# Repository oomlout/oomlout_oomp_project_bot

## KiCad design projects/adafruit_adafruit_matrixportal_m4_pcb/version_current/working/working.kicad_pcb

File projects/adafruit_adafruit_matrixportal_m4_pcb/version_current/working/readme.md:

# Adafruit-MatrixPortal-M4-PCB by adafruit  
This is a harvested standardized copy of a project from github.  
The original project can be found at:  
https://github.com/adafruit/Adafruit-MatrixPortal-M4-PCB  
Please consult that link for additional, details, files, and license information.  
Note: It was auto harvested and if the original repo had more than one board file or anything out of the ordinary the files here are likely not representative.

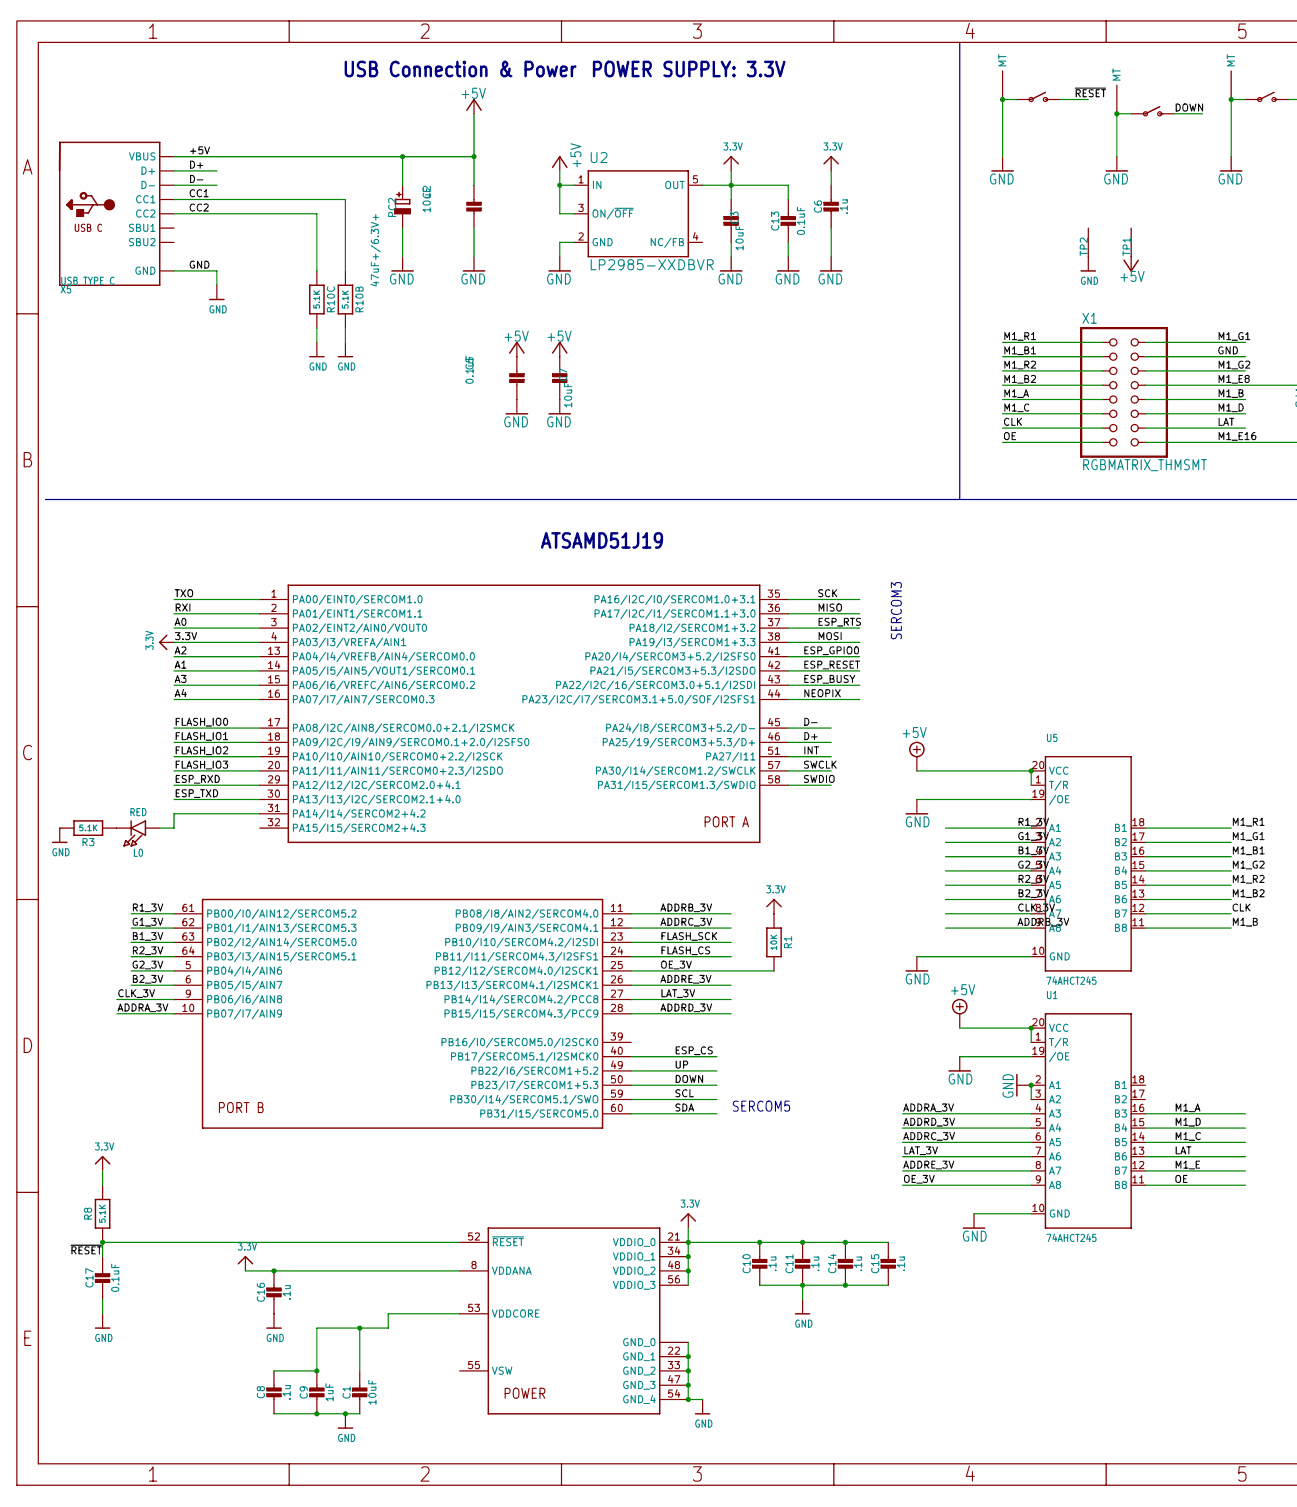
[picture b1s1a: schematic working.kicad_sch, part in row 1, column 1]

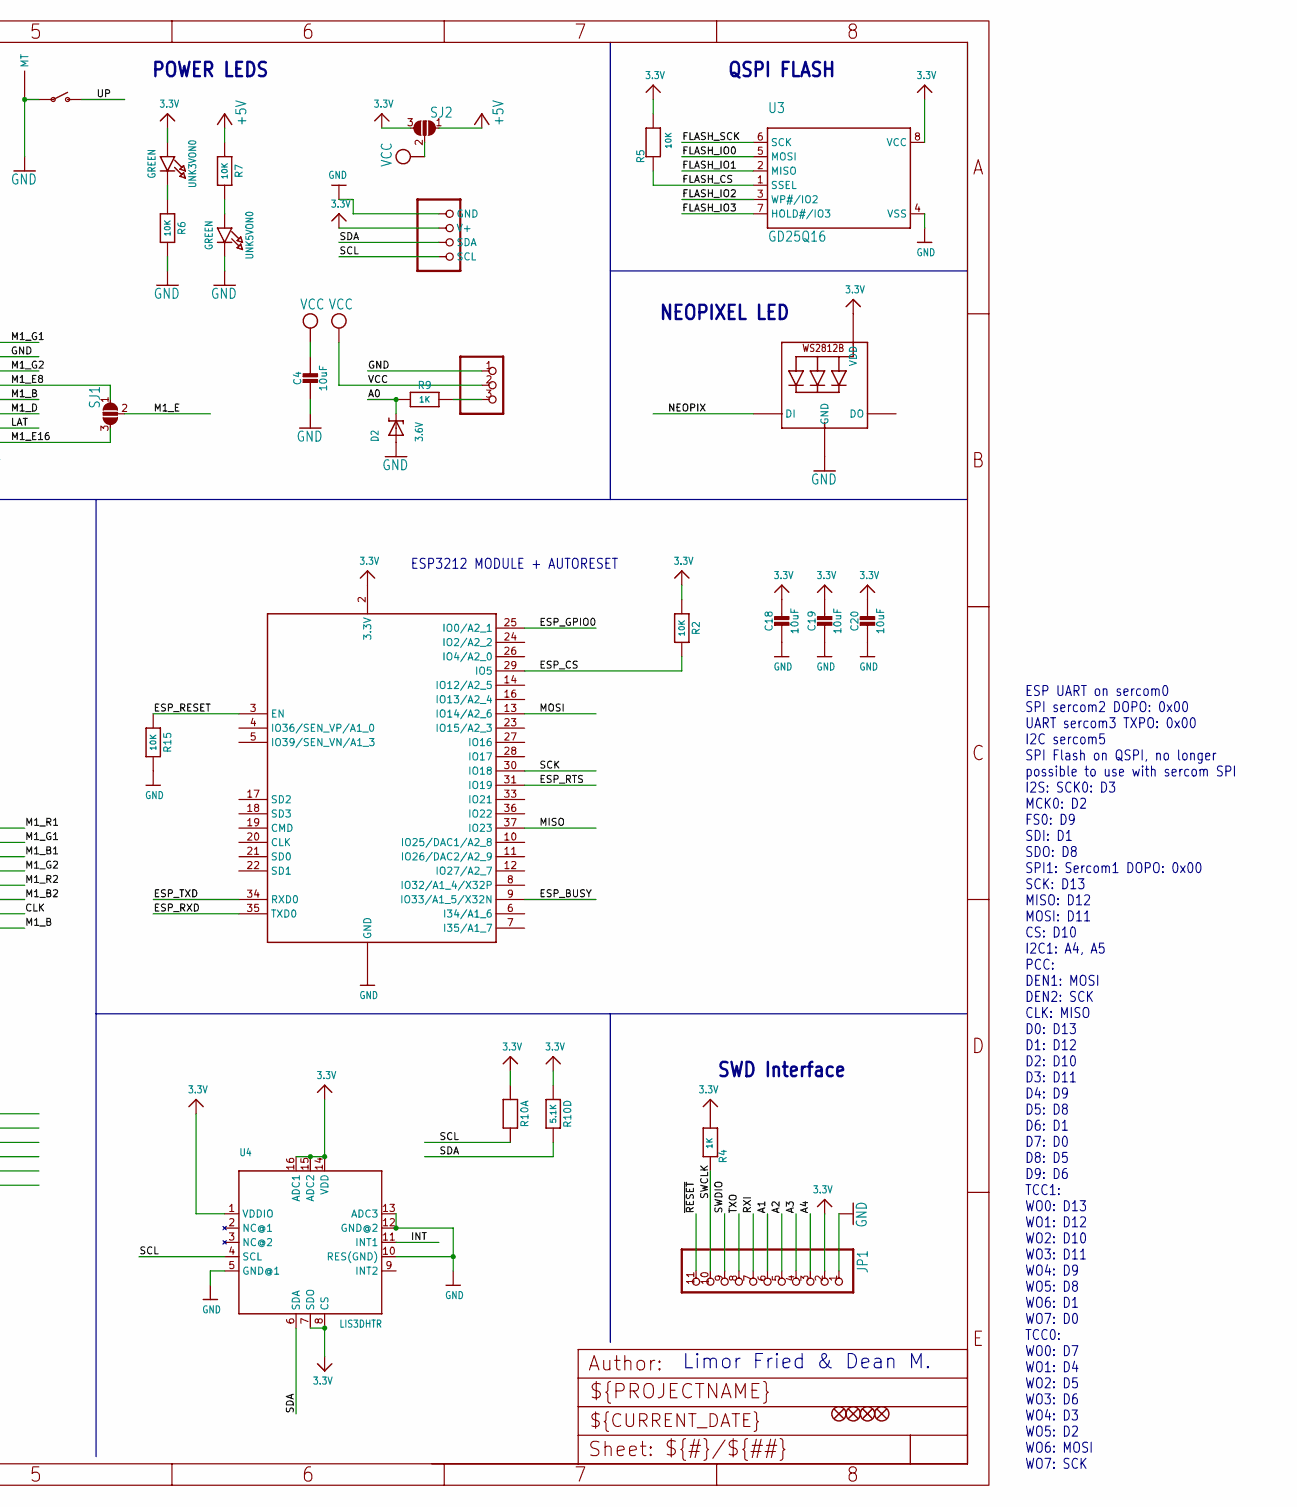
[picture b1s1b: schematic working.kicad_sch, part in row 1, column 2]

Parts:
C1, C2, C3, C4, C7, C18, C19, C20: 10uF; 0805-NO
C5, C13, C17: 0.1uF; 0603-NO
C6, C8, C10, C11, C14, C15, C16: .1u; 0603-NO
C9: 1uF; 0603-NO
CONN1: STEMMA_I2C_QT; JST_SH4
D2: 3.6V; SOD-323
DOWN0: TL3330AF260QG; SPST_TACTILE_RA
FID1, FID2, FID3, FID4: FIDUCIAL_1MM
JP1: HEADER-1X11; 1X11_ROUND
L0: RED; CHIPLED_0603_NOOUTLINE
LED1: WS2812B3535; LED3535
PC2: 47uF+/6.3V+; PANASONIC_D
R1, R2, R5, R6, R7, R15: 10K; 0603-NO
R3, R8: 5.1K; 0603-NO
R4, R9: 1K; 0603-NO
R10: 5.1K; RESPACK_4X0603
RST0: TL3330AF260QG; SPST_TACTILE_RA
SENSE0: JST PH 3; JSTPH3
SJ1, SJ2: SOLDERJUMPER_2WAY; SOLDERJUMPER_2WAY_OPEN_NOPASTE
TP1, TP2: SEWTAP_SMTNUTM3; SMT_NUT_3MM
U1, U5: 74AHCT245; TSSOP20
U2: LP2985-XXDBVR; SOT23-DBV
U3: GD25Q16; SOIC8_208MIL
U4: LIS3DHTR; LGA16_3X3MM
U$1: ATSAMD51J; PQFN64-1
UNK3VON0, UNK5VON0: GREEN; CHIPLED_0805_NOOUTLINE
UP0: TL3330AF260QG; SPST_TACTILE_RA
X1: RGBMATRIX_THMSMT; 2X08_SMTTHM_RGBMATRIX
X5: USB TYPE C; USB_C_CUSB31-CFM2AX-01-X
X6: ESP32_WROOM32; WROOM32

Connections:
3.3V: C3.2, C6.2, C10.2, C11.2, C13.1, C14.2, C15.2, C16.2, C18.1, C19.1, C20.1, CONN1.2 (V+), JP1.2, LED1.2 (VDD), R1.1, R2.1, R4.2, R5.2, R8.2, R10.1, R10.4 (1), SJ2.3, U2.5 (OUT), U3.8 (VCC), U4.1 (VDDIO), U4.7 (SDO), U4.8 (CS), U4.14 (VDD), U4.15 (ADC2), U4.16 (ADC1), U$1.4 (PA03/I3/VREFA/AIN1), U$1.8 (VDDANA), U$1.21 (VDDIO_0), U$1.34 (VDDIO_1), U$1.48 (VDDIO_2), U$1.56 (VDDIO_3), UNK3VON0.A, X6.2 (3.3V)
+5V: C2.2, C5.2, C7.2, PC2.+, R7.1, SJ2.1, TP1.P$1, U1.1 (T/R), U1.20 (VCC), U2.1 (IN), U2.3 (ON/~OFF), U5.1 (T/R), U5.20 (VCC), X5.A4B9 (VBUS), X5.B4A9 (VBUS)
A0: D2.C, R9.2, U$1.3 (PA02/EINT2/AIN0/VOUT0)
A0_JST: R9.1, SENSE0.3
A1: JP1.6, U$1.14 (PA05/I5/AIN5/VOUT1/SERCOM0.1)
A2: JP1.5, U$1.13 (PA04/I4/VREFB/AIN4/SERCOM0.0)
A3: JP1.4, U$1.15 (PA06/I6/VREFC/AIN6/SERCOM0.2)
A4: JP1.3, U$1.16 (PA07/I7/AIN7/SERCOM0.3)
ADDRA_3V: U1.4 (A3), U$1.10 (PB07/I7/AIN9)
ADDRB_3V: U5.9 (A8), U$1.11 (PB08/I8/AIN2/SERCOM4.0)
ADDRC_3V: U1.6 (A5), U$1.12 (PB09/I9/AIN3/SERCOM4.1)
ADDRD_3V: U1.5 (A4), U$1.28 (PB15/I15/SERCOM4.3/PCC9)
ADDRE_3V: U1.8 (A7), U$1.26 (PB13/I13/SERCOM4.1/I2SMCK1)
B1_3V: U5.4 (A3), U$1.63 (PB02/I2/AIN14/SERCOM5.0)
B2_3V: U5.7 (A6), U$1.6 (PB05/I5/AIN7)
CC1: R10.2 (1), X5.A5 (CC1)
CC2: R10.3 (1), X5.B5 (CC2)
CLK: U5.12 (B7), X1.13, X1.13S (13)
CLK_3V: U5.8 (A7), U$1.9 (PB06/I6/AIN8)
D+: U$1.46 (PA25/19/SERCOM3+5.3/D+), X5.A6 (D+), X5.B6 (D+)
D-: U$1.45 (PA24/I8/SERCOM3+5.2/D-), X5.A7 (D-), X5.B7 (D-)
DOWN: DOWN0.2 (S), U$1.50 (PB23/I7/SERCOM1+5.3)
ESP_BUSY: U$1.43 (PA22/I2C/16/SERCOM3.0+5.1/I2SDI), X6.9 (IO33/A1_5/X32N)
ESP_CS: R2.2, U$1.40 (PB17/SERCOM5.1/I2SMCK0), X6.29 (IO5)
ESP_GPIO0: U$1.41 (PA20/I4/SERCOM3+5.2/I2SFS0), X6.25 (IO0/A2_1)
ESP_RESET: R15.1, U$1.42 (PA21/I5/SERCOM3+5.3/I2SDO), X6.3 (EN)
ESP_RTS: U$1.37 (PA18/I2/SERCOM1+3.2), X6.31 (IO19)
ESP_RXD: U$1.29 (PA12/I12/I2C/SERCOM2.0+4.1), X6.35 (TXD0)
ESP_TXD: U$1.30 (PA13/I13/I2C/SERCOM2.1+4.0), X6.34 (RXD0)
FLASH_CS: R5.1, U3.1 (SSEL), U$1.24 (PB11/I11/SERCOM4.3/I2SFS1)
FLASH_IO0: U3.5 (MOSI), U$1.17 (PA08/I2C/AIN8/SERCOM0.0+2.1/I2SMCK)
FLASH_IO1: U3.2 (MISO), U$1.18 (PA09/I2C/I9/AIN9/SERCOM0.1+2.0/I2SFS0)
FLASH_IO2: U3.3 (WP#/IO2), U$1.19 (PA10/I10/AIN10/SERCOM0+2.2/I2SCK)
FLASH_IO3: U3.7 (HOLD#/IO3), U$1.20 (PA11/I11/AIN11/SERCOM0+2.3/I2SDO)
FLASH_SCK: U3.6 (SCK), U$1.23 (PB10/I10/SERCOM4.2/I2SDI)
G1_3V: U5.3 (A2), U$1.62 (PB01/I1/AIN13/SERCOM5.3)
G2_3V: U5.5 (A4), U$1.5 (PB04/I4/AIN6)
GND: C1.2, C2.1, C3.1, C4.2, C5.1, C6.1, C7.1, C8.1, C9.2, C10.1, C11.1, C13.2, C14.1, C15.1, C16.1, C17.1, C18.2, C19.2, C20.2, CONN1.1 (GND), D2.A, DOWN0.1, DOWN0.MT1 (MT), DOWN0.MT2 (MT), JP1.1, LED1.4 (GND), PC2.-, R3.2, R6.2, R10.6 (2), R10.7 (2), R15.2, RST0.1, RST0.MT1 (MT), RST0.MT2 (MT), SENSE0.1, TP2.P$1, U1.2 (A1), U1.3 (A2), U1.10 (GND), U1.19 (/OE), U2.2 (GND), U3.4 (VSS), U4.5 (GND@1), U4.10 (RES(GND)), U4.12 (GND@2), U4.13 (ADC3), U5.10 (GND), U5.19 (/OE), U$1.7 (GND_0), U$1.22 (GND_1), U$1.33 (GND_2), U$1.47 (GND_3), U$1.54 (GND_4), U$1.EXP (GND_0), UNK5VON0.C, UP0.1, UP0.MT1 (MT), UP0.MT2 (MT), X1.4, X1.4S (4), X5.A1B12 (GND), X5.B1A12 (GND), X6.1 (GND), X6.15 (GND), X6.38 (GND), X6.P$1 (GND)
INT: U4.11 (INT1), U$1.51 (PA27/I11)
LAT: U1.13 (B6), X1.14, X1.14S (14)
LAT_3V: U1.7 (A6), U$1.27 (PB14/I14/SERCOM4.2/PCC8)
M1_A: U1.16 (B3), X1.9, X1.9S (9)
M1_B: U5.11 (B8), X1.10, X1.10S (10)
M1_B1: U5.16 (B3), X1.3, X1.3S (3)
M1_B2: U5.13 (B6), X1.7, X1.7S (7)
M1_C: U1.14 (B5), X1.11, X1.11S (11)
M1_D: U1.15 (B4), X1.12, X1.12S (12)
M1_E: SJ1.2, U1.12 (B7)
M1_E8: SJ1.1, X1.8, X1.8S (8)
M1_E16: SJ1.3, X1.16, X1.16S (16)
M1_G1: U5.17 (B2), X1.2, X1.2S (2)
M1_G2: U5.15 (B4), X1.6, X1.6S (6)
M1_R1: U5.18 (B1), X1.1, X1.1S (1)
M1_R2: U5.14 (B5), X1.5, X1.5S (5)
MISO: U$1.36 (PA17/I2C/I1/SERCOM1.1+3.0), X6.37 (IO23)
MOSI: U$1.38 (PA19/I3/SERCOM1+3.3), X6.13 (IO14/A2_6)
unnamed: R7.2, UNK5VON0.A
unnamed: R6.1, UNK3VON0.C
unnamed: L0.A, U$1.31 (PA14/I14/SERCOM2+4.2)
unnamed: L0.C, R3.1
NEOPIX: LED1.1 (DI), U$1.44 (PA23/I2C/I7/SERCOM3.1+5.0/SOF/I2SFS1)
OE: U1.11 (B8), X1.15, X1.15S (15)
OE_3V: R1.2, U1.9 (A8), U$1.25 (PB12/I12/SERCOM4.0/I2SCK1)
R1_3V: U5.2 (A1), U$1.61 (PB00/I0/AIN12/SERCOM5.2)
R2_3V: U5.6 (A5), U$1.64 (PB03/I3/AIN15/SERCOM5.1)
RXI: JP1.7, U$1.2 (PA01/EINT1/SERCOM1.1)
SCK: U$1.35 (PA16/I2C/I0/SERCOM1.0+3.1), X6.30 (IO18)
SCL: CONN1.4 (SCL), R10.8 (2), U4.4 (SCL), U$1.59 (PB30/I14/SERCOM5.1/SWO)
SDA: CONN1.3 (SDA), R10.5 (2), U4.6 (SDA), U$1.60 (PB31/I15/SERCOM5.0)
SWCLK: JP1.10, R4.1, U$1.57 (PA30/I14/SERCOM1.2/SWCLK)
SWDIO: JP1.9, U$1.58 (PA31/I15/SERCOM1.3/SWDIO)
TXO: JP1.8, U$1.1 (PA00/EINT0/SERCOM1.0)
UP: U$1.49 (PB22/I6/SERCOM1+5.2), UP0.2 (S)
VCC: C4.1, SENSE0.2, SJ2.2
VDDCORE: C1.1, C8.2, C9.1, U$1.53 (VDDCORE)
~RESET: C17.2, JP1.11, R8.1, RST0.2 (S), U$1.52 (~RESET)

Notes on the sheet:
Limor Fried & Dean M.
ESP UART on sercom0 SPI sercom2 DOPO: 0x00 UART sercom3 TXPO: 0x00 I2C sercom5 SPI Flash on QSPI, no longer possible to use with sercom SPI I2S: SCK0: D3 MCK0: D2 FS0: D9 SDI: D1 SDO: D8 SPI1: Sercom1 DOPO: 0x00 SCK: D13 MISO: D12 MOSI: D11 CS: D10 I2C1: A4, A5 PCC: DEN1: MOSI DEN2: SCK CLK: MISO D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
POWER LEDS
ATSAMD51J19
SERCOM3
USB Connection & Power
SWD Interface
QSPI FLASH
ESP3212 MODULE + AUTORESET
SERCOM5
POWER SUPPLY: 3.3V
NEOPIXEL LED

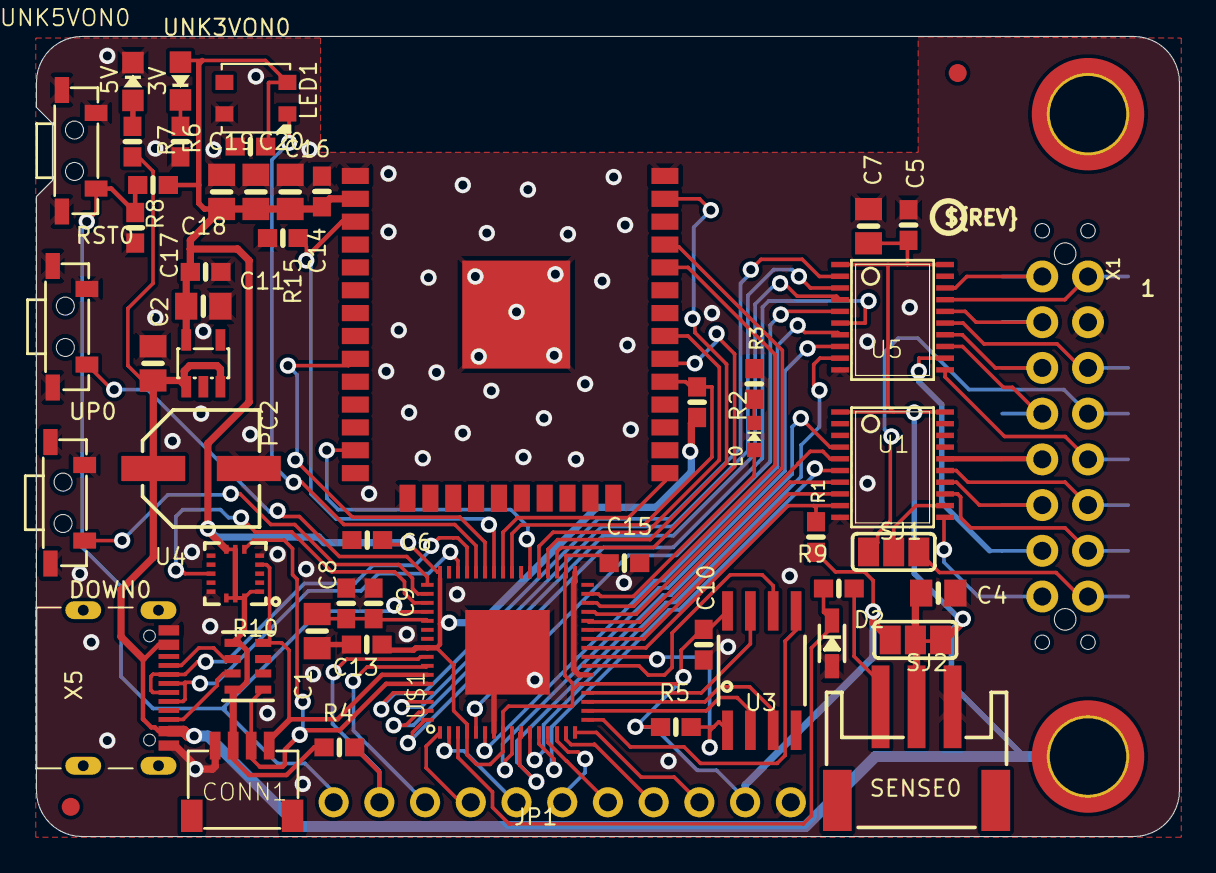
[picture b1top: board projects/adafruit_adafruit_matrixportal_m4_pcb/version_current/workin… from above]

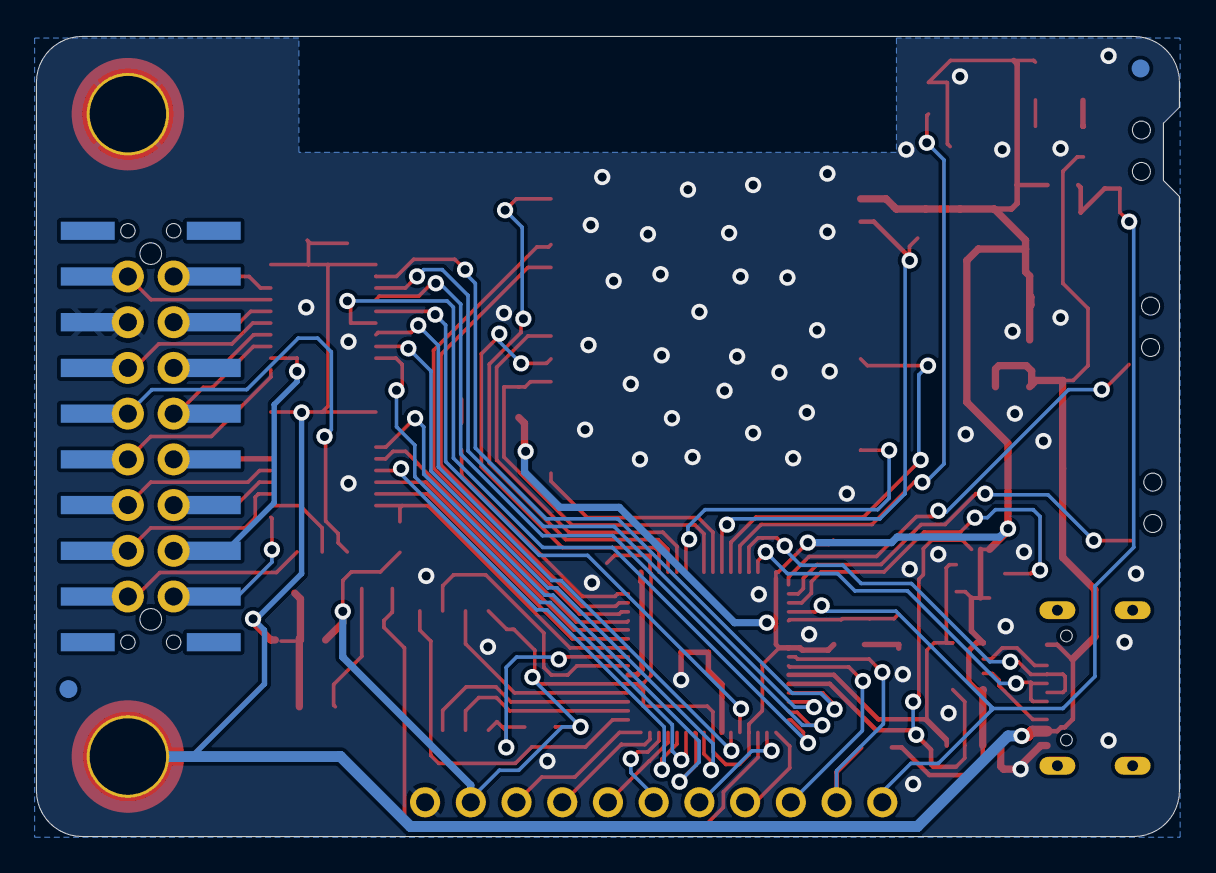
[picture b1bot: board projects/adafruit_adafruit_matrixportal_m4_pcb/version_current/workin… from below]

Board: 2 copper layers, 63.5 x 44.5 mm, 62 parts (3 on the bottom side), 76 nets.

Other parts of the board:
U$41: MATRIXPORTAL_BOT
U$44: PCBFEAT-REV-040
U$45: MATRIXPORTAL_TOP

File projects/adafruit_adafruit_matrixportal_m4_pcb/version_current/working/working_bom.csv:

Row,Description,Part,References,Value,Footprint,Quantity Per PCB,Status,Datasheet
1,,CAP_CERAMIC0603_NO,C5 C6 C8 C10 C11 C13 C14 C15 C16 C17,0.1uF,0603-NO,10, ,
2,,CAP_CERAMIC0603_NO,C9,1uF,0603-NO,1, ,
3,,CAP_CERAMIC0805-NOOUTLINE,C1 C2 C3 C4 C7 C18 C19 C20,10uF,0805-NO,8, ,
4,,STEMMA_I2C_QT,CONN1,STEMMA_I2C_QT,JST_SH4,1, ,
5,,DIODE-ZENERSOD323,D2,3.6V,SOD-323,1, ,
6,,SWITCH_SPST_TACT_RA,DOWN0 RST0 UP0,TL3330AF260QG,SPST_TACTILE_RA,3, ,
7,,HEADER-1X11,JP1,HEADER-1X11,1X11_ROUND,1, ,
8,,LED0603_NOOUTLINE,L0,RED,CHIPLED_0603_NOOUTLINE,1, ,
9,,WS2812B3535,LED1,WS2812B3535,LED3535,1, ,
10,,CAP_ELECTROLYTICPANASONIC_D,PC2,47uF+/6.3V+,PANASONIC_D,1, ,
11,,RESISTOR_0603_NOOUT,R4 R9,1K,0603-NO,2, ,
12,,RESISTOR_4PACK,R10,5.1K,RESPACK_4X0603,1, ,
13,,RESISTOR_0603_NOOUT,R3 R8,5.1K,0603-NO,2, ,
14,,RESISTOR_0603_NOOUT,R1 R2 R5 R6 R7 R15,10K,0603-NO,6, ,
15,,CON_JST_PH_3PIN,SENSE0,JST PH 3,JSTPH3,1, ,
16,,74LCX245,U1 U5,74AHCT245,TSSOP20,2, ,
17,,SPIFLASH_8PIN208MIL,U3,GD25Q16,SOIC8_208MIL,1, ,
18,,ACCEL_LIS3DHTR,U4,LIS3DHTR,LGA16_3X3MM,1, ,
19,,LP2985-XXDBVR,U2,LP2985-XXDBVR,SOT23-DBV,1, ,
20,,ATSAMD51J,U$1,ATSAMD51J,PQFN64-1,1, ,
21,,LED0805_NOOUTLINE,UNK3VON0 UNK5VON0,GREEN,CHIPLED_0805_NOOUTLINE,2, ,
22,,ESP32_WROOM32,X6,ESP32_WROOM32,WROOM32,1, ,
23,,RGBMATRIX_THMSMT,X1,RGBMATRIX_THMSMT,2X08_SMTTHM_RGBMATRIX,1, ,
24,,USB_C,X5,USB TYPE C,USB_C_CUSB31-CFM2AX-01-X,1, ,





Project info:
Schematic:,working
Variant:,default
Revision:,
Date:,2023-08-03_17-21-22
KiCad Version:,7.0.6-7.0.6~ubuntu22.04.1
Statistics:
Component Groups:,24
Component Count:,51 (0 SMD/ 0 THT)
Fitted Components:,51 (0 SMD/ 0 THT)
Number of PCBs:,1
Total Components:,51

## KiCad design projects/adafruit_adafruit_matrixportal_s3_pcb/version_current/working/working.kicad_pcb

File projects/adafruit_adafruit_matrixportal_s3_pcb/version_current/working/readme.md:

# Adafruit-MatrixPortal-S3-PCB by adafruit  
This is a harvested standardized copy of a project from github.  
The original project can be found at:  
https://github.com/adafruit/Adafruit-MatrixPortal-S3-PCB  
Please consult that link for additional, details, files, and license information.  
Note: It was auto harvested and if the original repo had more than one board file or anything out of the ordinary the files here are likely not representative.

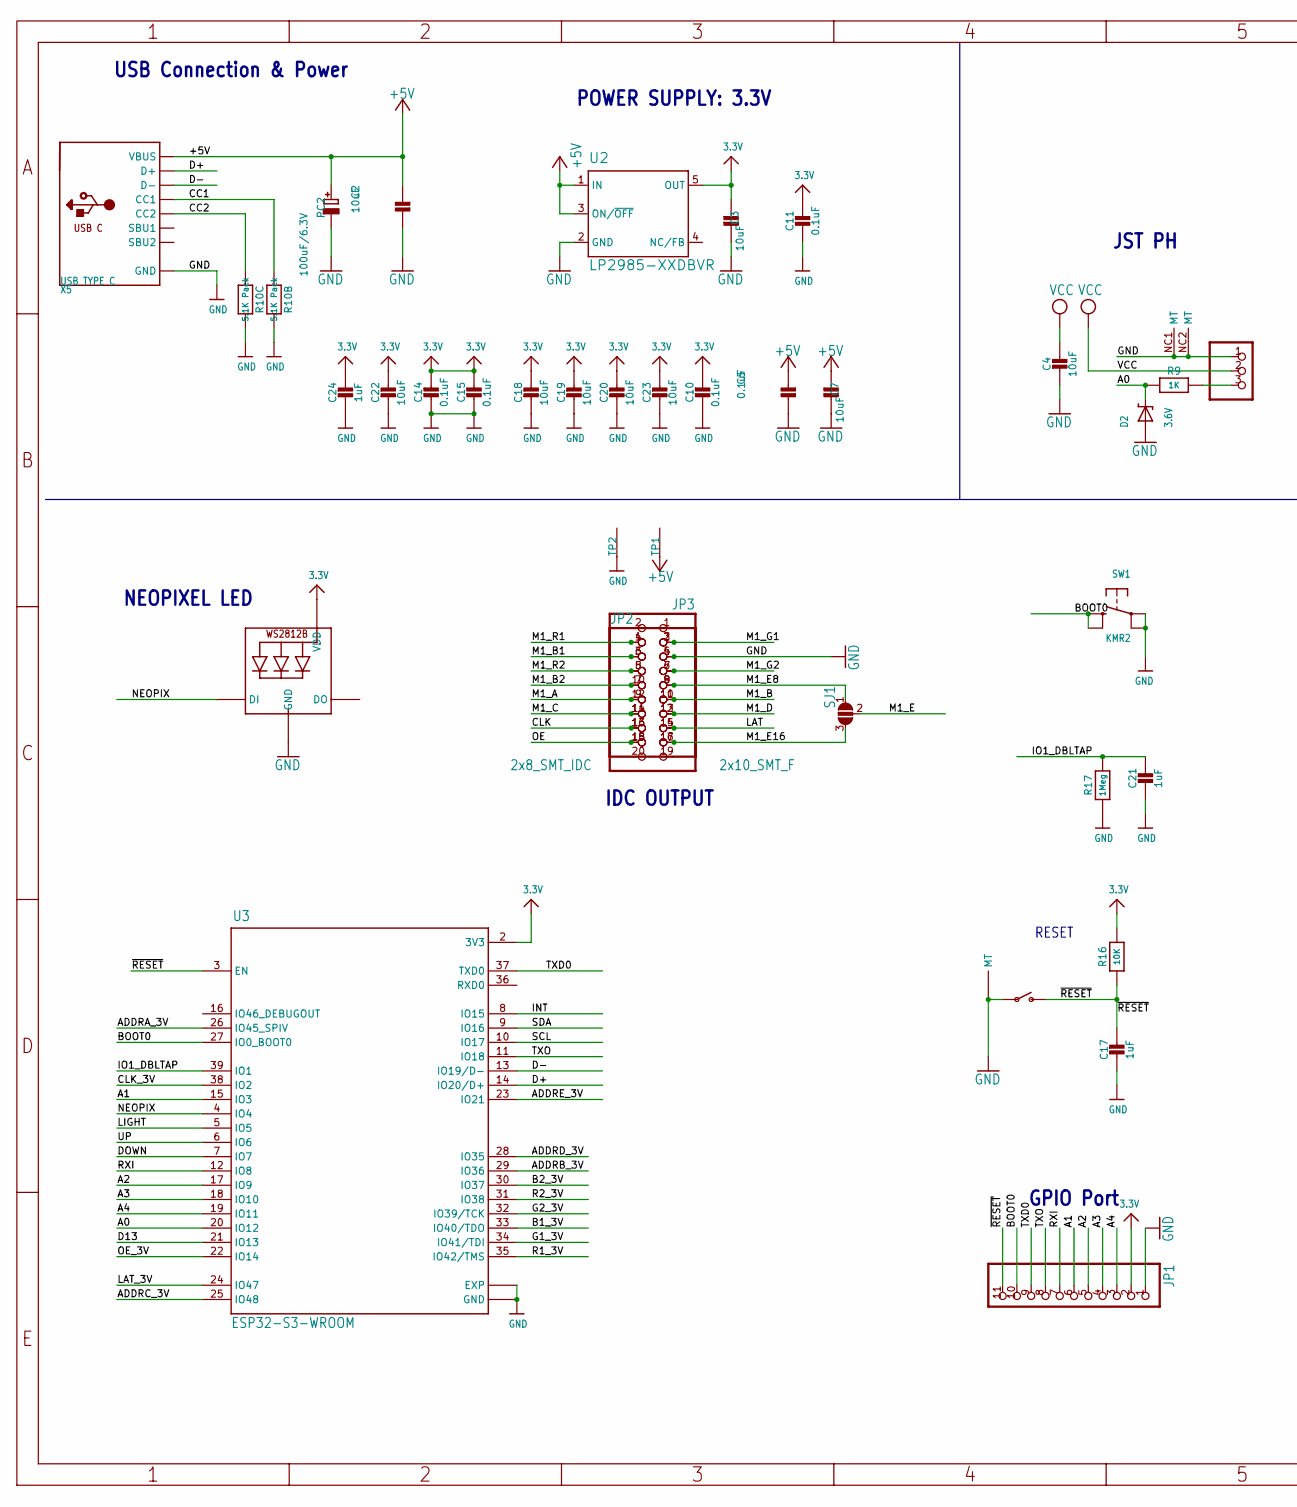
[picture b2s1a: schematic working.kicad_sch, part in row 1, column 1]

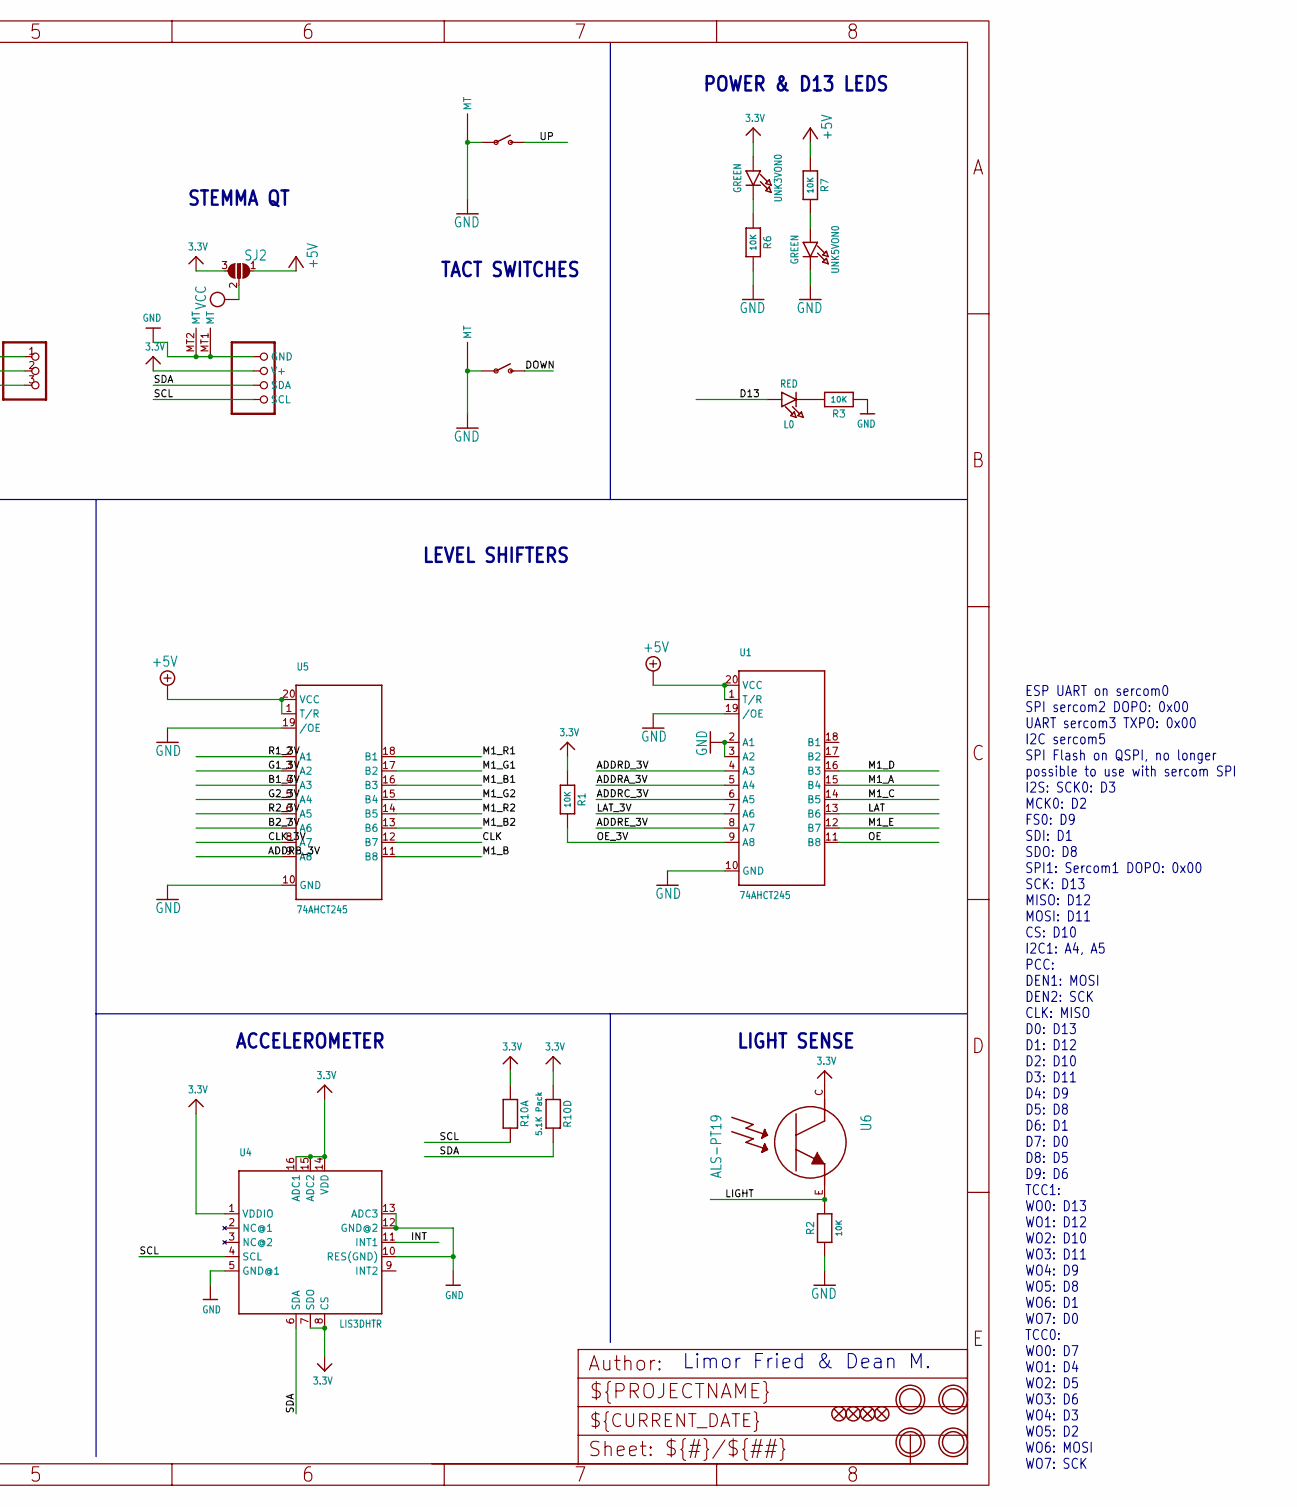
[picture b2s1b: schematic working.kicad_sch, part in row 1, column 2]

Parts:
C2, C3, C4, C7, C18, C19, C20, C22, C23: 10uF; 0805-NO
C5, C10, C11, C14, C15: 0.1uF; 0603-NO
C17, C21, C24: 1uF; 0603-NO
CONN1: STEMMA_I2C_QT; JST_SH4
D2: 3.6V; SOD-323
DOWN0: TL3330AF260QG; SPST_TACTILE_RA
FID1, FID2, FID3, FID4: FIDUCIAL_1MM
JP1: HEADER-1X11; 1X11_ROUND
JP2: 2x8_SMT_IDC; 2X08_SHROUDEDSMT
JP3: 2x10_SMT_F; 2X10_SMT_FEMALE
L0: RED; CHIPLED_0603_NOOUTLINE
LED1: WS2812B_3535FULL; LED3535_FULLPADS
PC2: 100uF/6.3V; PANASONIC_D
R1, R2, R3, R6, R7, R16: 10K; 0603-NO
R9: 1K; 0603-NO
R10: 5.1K Pack; RESPACK_4X0603
R17: 1Meg; 0603-NO
RST0: TL3330AF260QG; SPST_TACTILE_RA
SENSE0: JST PH 3; JSTPH3
SJ1, SJ2: SOLDERJUMPER_2WAY; SOLDERJUMPER_2WAY_OPEN_NOPASTE
SW1: KMR2; BTN_RKB2_4.6X2.8
TP1, TP2: SEWTAP_SMTNUTM3; SMT_NUT_3MM
U1, U5: 74AHCT245; TSSOP20
U2: LP2985-XXDBVR; SOT23-DBV
U3: ESP32-S3-WROOM; S3-WROOM32
U4: LIS3DHTR; LGA16_3X3MM
U6: ALS-PT19; ALS-PT19-315C
U$14, U$19, U$22, U$24: MOUNTINGHOLE2.5; MOUNTINGHOLE_2.5_PLATED
UNK3VON0, UNK5VON0: GREEN; CHIPLED_0603_NOOUTLINE
UP0: TL3330AF260QG; SPST_TACTILE_RA
X5: USB TYPE C; USB_C_CUSB31-CFM2AX-01-X

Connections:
3.3V: C3.2, C10.2, C11.2, C14.2, C15.2, C18.1, C19.1, C20.1, C22.1, C23.1, C24.1, CONN1.2 (V+), JP1.2, LED1.2 (VDD), R1.1, R10.1, R10.4 (1), R16.2, SJ2.3, U2.5 (OUT), U3.2 (3V3), U4.1 (VDDIO), U4.7 (SDO), U4.8 (CS), U4.14 (VDD), U4.15 (ADC2), U4.16 (ADC1), U6.C, UNK3VON0.A
+5V: C2.2, C5.2, C7.2, PC2.+, R7.1, SJ2.1, TP1.P$1, U1.1 (T/R), U1.20 (VCC), U2.1 (IN), U2.3 (ON/~OFF), U5.1 (T/R), U5.20 (VCC), X5.A4B9 (VBUS), X5.B4A9 (VBUS)
A0: D2.C, R9.2, U3.20 (IO12)
A0_JST: R9.1, SENSE0.3
A1: JP1.6, U3.15 (IO3)
A2: JP1.5, U3.17 (IO9)
A3: JP1.4, U3.18 (IO10)
A4: JP1.3, U3.19 (IO11)
ADDRA_3V: U1.5 (A4), U3.26 (IO45_SPIV)
ADDRB_3V: U3.29 (IO36), U5.9 (A8)
ADDRC_3V: U1.6 (A5), U3.25 (IO48)
ADDRD_3V: U1.4 (A3), U3.28 (IO35)
ADDRE_3V: U1.8 (A7), U3.23 (IO21)
B1_3V: U3.33 (IO40/TDO), U5.4 (A3)
B2_3V: U3.30 (IO37), U5.7 (A6)
BOOT0: JP1.10, SW1.B (S), SW1.B' (S1), U3.27 (IO0_BOOT0)
CC1: R10.2 (1), X5.A5 (CC1)
CC2: R10.3 (1), X5.B5 (CC2)
CLK: JP2.13, JP3.16, U5.12 (B7)
CLK_3V: U3.38 (IO2), U5.8 (A7)
D13: L0.A, U3.21 (IO13)
D+: U3.14 (IO20/D+), X5.A6 (D+), X5.B6 (D+)
D-: U3.13 (IO19/D-), X5.A7 (D-), X5.B7 (D-)
DOWN: DOWN0.2 (S), U3.7 (IO7)
G1_3V: U3.34 (IO41/TDI), U5.3 (A2)
G2_3V: U3.32 (IO39/TCK), U5.5 (A4)
GND: C2.1, C3.1, C4.2, C5.1, C7.1, C10.1, C11.1, C14.1, C15.1, C17.2, C18.2, C19.2, C20.2, C21.2, C22.2, C23.2, C24.2, CONN1.1 (GND), CONN1.MT1 (MT), CONN1.MT2 (MT), D2.A, DOWN0.1, DOWN0.MT1 (MT), DOWN0.MT2 (MT), JP1.1, JP2.4, JP3.5, LED1.4 (GND), PC2.-, R2.2, R3.2, R6.2, R10.6 (2), R10.7 (2), R17.1, RST0.1, RST0.MT1 (MT), RST0.MT2 (MT), SENSE0.1, SENSE0.NC1 (MT), SENSE0.NC2 (MT), SW1.A, SW1.A' (P1), TP2.P$1, U1.2 (A1), U1.3 (A2), U1.10 (GND), U1.19 (/OE), U2.2 (GND), U3.1 (GND), U3.40 (GND), U3.P$2 (EXP), U3.P$3 (EXP), U3.P$4 (EXP), U3.P$5 (EXP), U3.P$6 (EXP), U3.P$7 (EXP), U3.P$8 (EXP), U3.P$9 (EXP), U3.P$10 (EXP), U4.5 (GND@1), U4.10 (RES(GND)), U4.12 (GND@2), U4.13 (ADC3), U5.10 (GND), U5.19 (/OE), UNK5VON0.C, UP0.1, UP0.MT1 (MT), UP0.MT2 (MT), X5.A1B12 (GND), X5.B1A12 (GND)
INT: U3.8 (IO15), U4.11 (INT1)
IO1_DBLTAP: C21.1, R17.2, U3.39 (IO1)
LAT: JP2.14, JP3.15, U1.13 (B6)
LAT_3V: U1.7 (A6), U3.24 (IO47)
LIGHT: R2.1, U3.5 (IO5), U6.E
M1_A: JP2.9, JP3.12, U1.15 (B4)
M1_B: JP2.10, JP3.11, U5.11 (B8)
M1_B1: JP2.3, JP3.6, U5.16 (B3)
M1_B2: JP2.7, JP3.10, U5.13 (B6)
M1_C: JP2.11, JP3.14, U1.14 (B5)
M1_D: JP2.12, JP3.13, U1.16 (B3)
M1_E: SJ1.2, U1.12 (B7)
M1_E8: JP2.8, JP3.9, SJ1.1
M1_E16: JP2.16, JP3.17, SJ1.3
M1_G1: JP2.2, JP3.3, U5.17 (B2)
M1_G2: JP2.6, JP3.7, U5.15 (B4)
M1_R1: JP2.1, JP3.4, U5.18 (B1)
M1_R2: JP2.5, JP3.8, U5.14 (B5)
unnamed: R7.2, UNK5VON0.A
unnamed: R6.1, UNK3VON0.C
unnamed: L0.C, R3.1
NEOPIX: LED1.1 (DI), U3.4 (IO4)
OE: JP2.15, JP3.18, U1.11 (B8)
OE_3V: R1.2, U1.9 (A8), U3.22 (IO14)
R1_3V: U3.35 (IO42/TMS), U5.2 (A1)
R2_3V: U3.31 (IO38), U5.6 (A5)
RXI: JP1.7, U3.12 (IO8)
SCL: CONN1.4 (SCL), R10.8 (2), U3.10 (IO17), U4.4 (SCL)
SDA: CONN1.3 (SDA), R10.5 (2), U3.9 (IO16), U4.6 (SDA)
TXD0: JP1.9, U3.37 (TXD0)
TXO: JP1.8, U3.11 (IO18)
UP: U3.6 (IO6), UP0.2 (S)
VCC: C4.1, SENSE0.2, SJ2.2
~RESET: C17.1, JP1.11, R16.1, RST0.2 (S), U3.3 (EN)

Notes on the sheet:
JST PH
POWER SUPPLY: 3.3V
LIGHT SENSE
POWER & D13 LEDS
TACT SWITCHES
NEOPIXEL LED
LEVEL SHIFTERS
Limor Fried & Dean M.
RESET
IDC OUTPUT
ACCELEROMETER
USB Connection & Power
ESP UART on sercom0 SPI sercom2 DOPO: 0x00 UART sercom3 TXPO: 0x00 I2C sercom5 SPI Flash on QSPI, no longer possible to use with sercom SPI I2S: SCK0: D3 MCK0: D2 FS0: D9 SDI: D1 SDO: D8 SPI1: Sercom1 DOPO: 0x00 SCK: D13 MISO: D12 MOSI: D11 CS: D10 I2C1: A4, A5 PCC: DEN1: MOSI DEN2: SCK CLK: MISO D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
GPIO Port
STEMMA QT

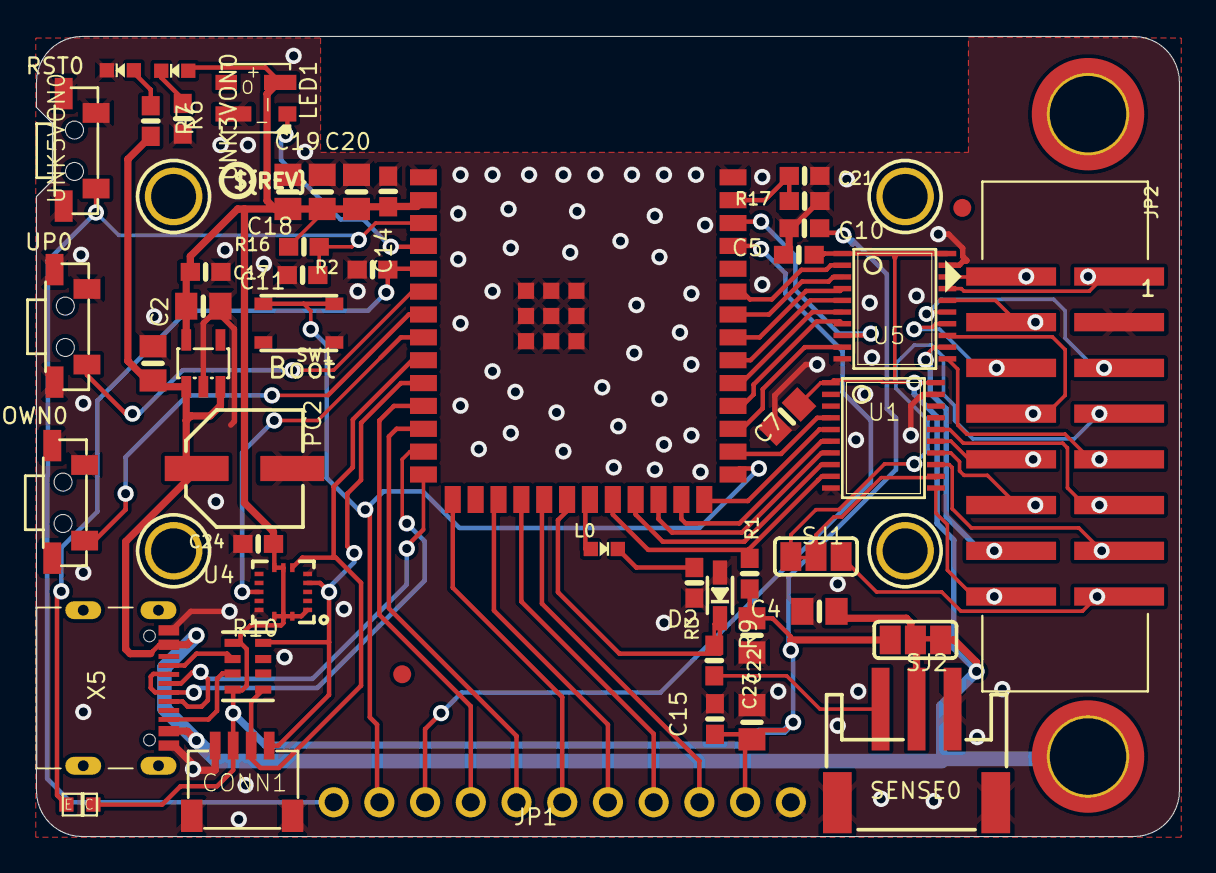
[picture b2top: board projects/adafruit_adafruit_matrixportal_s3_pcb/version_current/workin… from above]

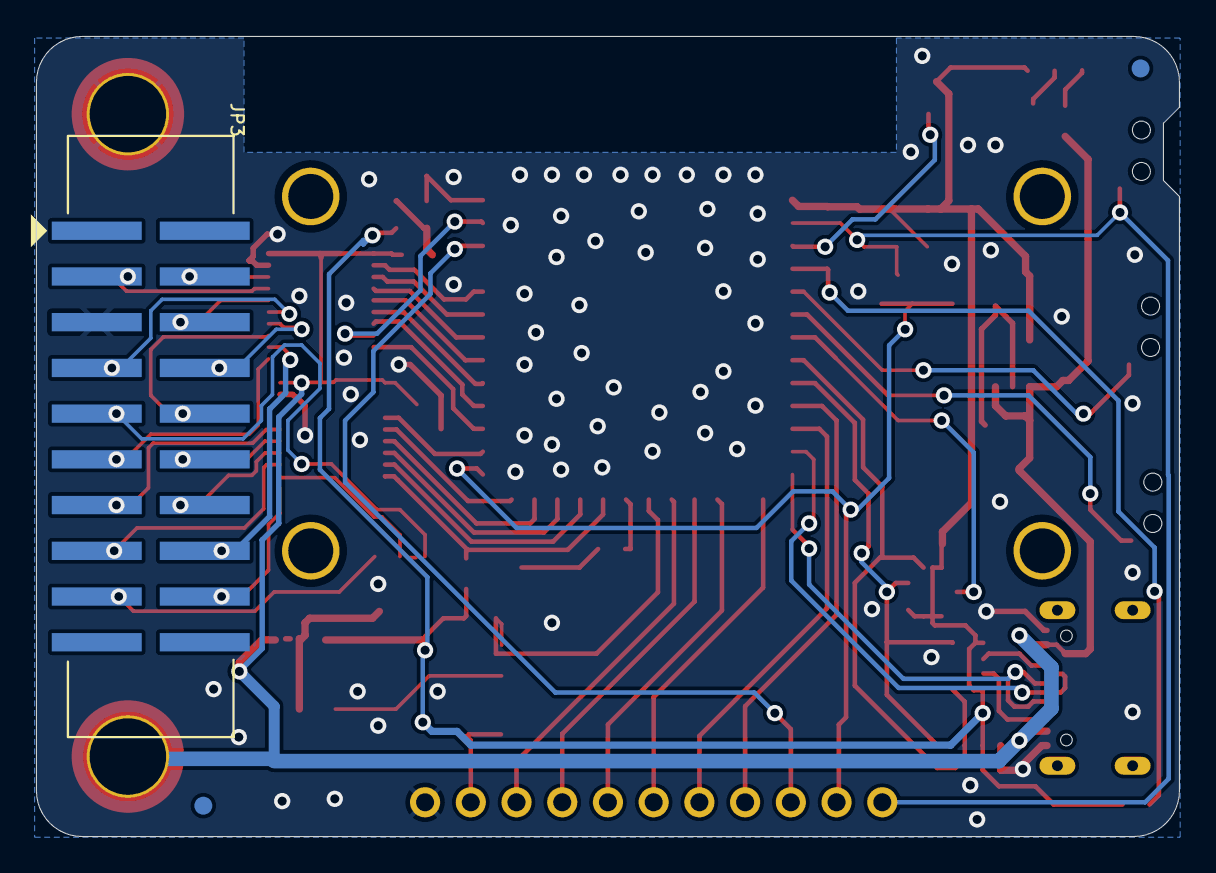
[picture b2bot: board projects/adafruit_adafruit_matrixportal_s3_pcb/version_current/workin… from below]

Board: 2 copper layers, 63.5 x 44.5 mm, 63 parts (4 on the bottom side), 61 nets.

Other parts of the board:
U$25: S3_MATRIXPORTAL_TOP
U$26: S3_MATRIXPORTAL_BOT
U$44: PCBFEAT-REV-040

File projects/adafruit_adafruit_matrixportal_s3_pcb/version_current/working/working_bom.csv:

Row,Description,Part,References,Value,Footprint,Quantity Per PCB,Status,Datasheet
1,,CAP_CERAMIC0603_NO,C5 C10 C11 C14 C15,0.1uF,0603-NO,5, ,
2,,CAP_CERAMIC0603_NO,C17 C21 C24,1uF,0603-NO,3, ,
3,,CAP_CERAMIC0805-NOOUTLINE,C2 C3 C4 C7 C18 C19 C20 C22 C23,10uF,0805-NO,9, ,
4,,STEMMA_I2C_QT,CONN1,STEMMA_I2C_QT,JST_SH4,1, ,
5,,DIODE-ZENERSOD323,D2,3.6V,SOD-323,1, ,
6,,SWITCH_SPST_MNT_TACT_RA,DOWN0 RST0 UP0,TL3330AF260QG,SPST_TACTILE_RA,3, ,
7,,HEADER-2X10SMT_FEMALE,JP3,2x10_SMT_F,2X10_SMT_FEMALE,1, ,
8,,HEADER-2X8_SHROUDEDSMT,JP2,2x8_SMT_IDC,2X08_SHROUDEDSMT,1, ,
9,,HEADER-1X11,JP1,HEADER-1X11,1X11_ROUND,1, ,
10,,LED0603_NOOUTLINE,L0,RED,CHIPLED_0603_NOOUTLINE,1, ,
11,,WS2812B_3535FULL,LED1,WS2812B_3535FULL,LED3535_FULLPADS,1, ,
12,,CAP_ELECTROLYTICPANASONIC_D,PC2,100uF/6.3V,PANASONIC_D,1, ,
13,,RESISTOR_0603_NOOUT,R9,1K,0603-NO,1, ,
14,,RESISTOR_4PACK,R10,5.1K Pack,RESPACK_4X0603,1, ,
15,,RESISTOR_0603_NOOUT,R1 R2 R3 R6 R7 R16,10K,0603-NO,6, ,
16,,RESISTOR_0603_NOOUT,R17,1Meg,0603-NO,1, ,
17,,CON_JST_PH_3PIN,SENSE0,JST PH 3,JSTPH3,1, ,
18,,SWITCH_TACT_SMT_RKB2,SW1,KMR2,BTN_RKB2_4.6X2.8,1, ,
19,,74LCX245_TSSOP20,U1 U5,74AHCT245,TSSOP20,2, ,
20,,PHOTOTRANSISTOR_PT19-315C,U6,ALS-PT19,ALS-PT19-315C,1, ,
21,,ESP32-S3-WROOM,U3,ESP32-S3-WROOM,S3-WROOM32,1, ,
22,,ACCEL_LIS3DHTR,U4,LIS3DHTR,LGA16_3X3MM,1, ,
23,,LP2985-XXDBVR,U2,LP2985-XXDBVR,SOT23-DBV,1, ,
24,,LED0603_NOOUTLINE,UNK3VON0 UNK5VON0,GREEN,CHIPLED_0603_NOOUTLINE,2, ,
25,,USB_C,X5,USB TYPE C,USB_C_CUSB31-CFM2AX-01-X,1, ,





Project info:
Schematic:,working
Variant:,default
Revision:,
Date:,2023-08-03_17-21-22
KiCad Version:,7.0.6-7.0.6~ubuntu22.04.1
Statistics:
Component Groups:,25
Component Count:,48 (0 SMD/ 0 THT)
Fitted Components:,48 (0 SMD/ 0 THT)
Number of PCBs:,1
Total Components:,48
